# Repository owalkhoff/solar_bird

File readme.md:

# solar bird

## What is a solar bird?

There are many species of solar birds. This one (like most) feeds on sunlight through a solar cell. Its brain is made up of an ATtiny13 microcontroller. With the help of a computer (and a human) it can learn new songs. A piezo speaker is the bird's voice. A resistor limits the inrush current through the piezo when the bird starts singing. And a capacitor supplies food during shady periods.

## Code

The solar bird can be programmed via the ISP header using a [USBasp programmer](https://www.fischl.de/usbasp/) and the command `make flash`.

The code can be found in [Urban Bieri's repository](https://github.com/schaum/solarBird). He developed it together with [Christoph Haberer (ChrisMicro)](https://github.com/ChrisMicro) based on Christoph's original code from 2008.

## Images

Here is a rendering of the PCB front, with components:

A beautiful solar bird made by a student at Kollegi Schwyz in September 2020 (workshop with Felix Bänteli, using an older PCB version):

## PDFs

The schematic:

[solar_bird_schematic.pdf](pdf/solar_bird_schematic.pdf)

Use a 3V or 4V solar cell.

## KiCad files

The schematic and layout were drawn in KiCad 5.1.8. You can find the project [in this directory](kicad).

I am experimenting with different PCB layouts that share the same schematic. Therefore there are three project files between which one can switch in the project tree (using the right mouse button):

* solar_bird.pro (to edit the schematic)
* solar_bird_pcb_01.pro (to edit layout version 1)
* solar_bird_pcb_02.pro (to edit layout version 2)

## License

CC .. ..

## To dos

* Arduino code as an alternative to main.c & makefile?
* Provide a guide for tweaking the code
* Program via [audio bootloader](https://github.com/ATtinyTeenageRiot/TinyAudioBoot) and corresponding hardware? (We likely need to switch to ATtiny45 or 85)
* Add alternative footprints for SMD components?
* Add labels in copper layer for DIY etched version
* Plot PDF and Gerber files for production
* Correct GitHub link in label on silkscreen layer
* Add license

## Research

* Where and when did this solar bird first appear - SGMK diy-makeaway? Who was there?

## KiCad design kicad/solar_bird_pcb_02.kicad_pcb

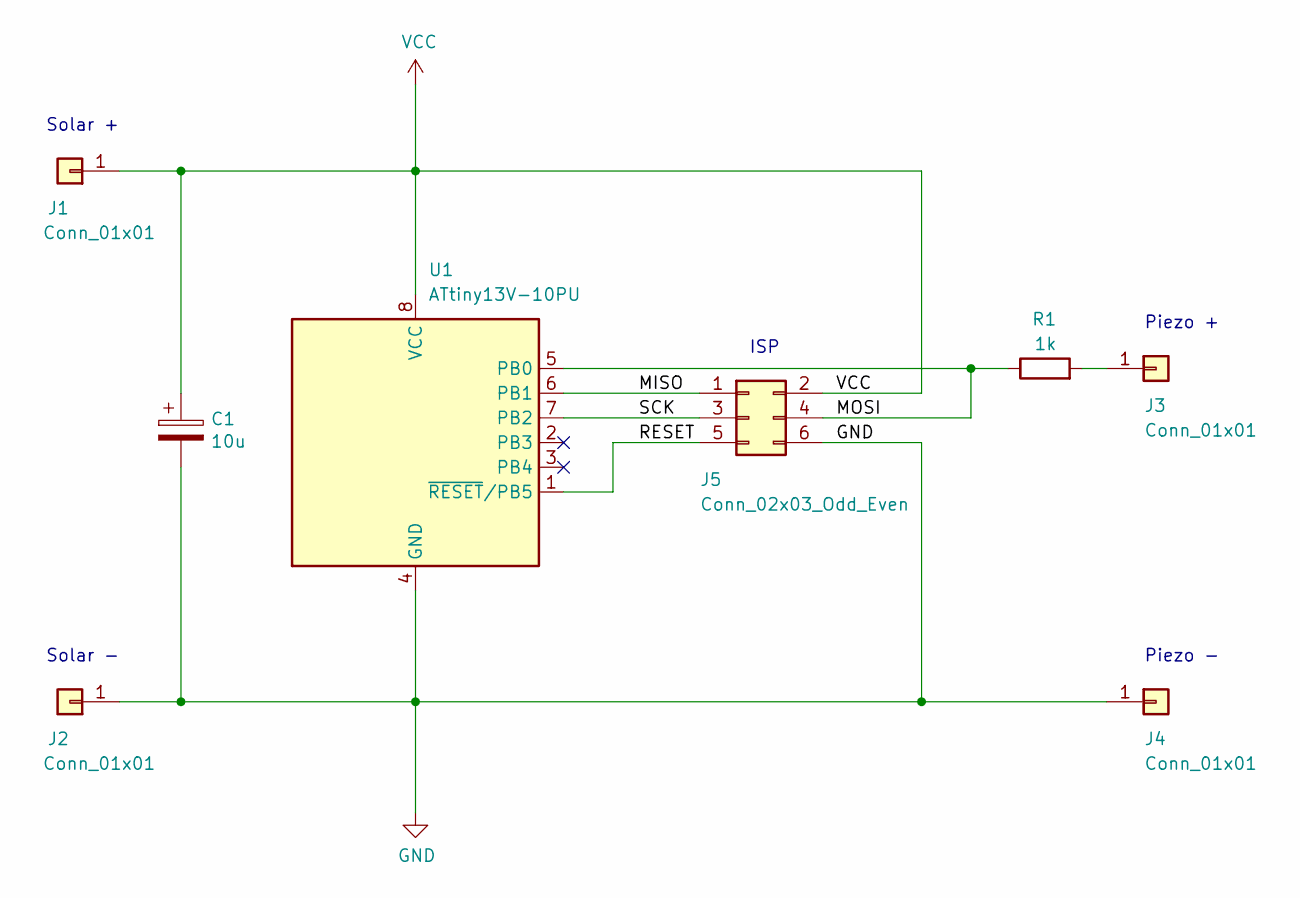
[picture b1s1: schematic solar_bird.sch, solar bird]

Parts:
C1: 10u; CP_Radial_D5.0mm_P2.50mm
J1, J2, J3, J4: Conn_01x01; Pin_D1.0mm_L10.0mm
J5: Conn_02x03_Odd_Even; PinHeader_2x03_P2.54mm_Vertical
R1: 1k; R_Axial_DIN0207_L6.3mm_D2.5mm_P10.16mm_Horizontal
U1: ATtiny13V-10PU; DIP-8_W7.62mm

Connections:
/MISO: J5.1, U1.6 (PB1)
/MOSI: J5.4, R1.1, U1.5 (PB0)
/RESET: J5.5, U1.1 (~RESET~/PB5)
/SCK: J5.3, U1.7 (PB2)
GND: C1.2, J2.1, J4.1, J5.6, U1.4 (GND)
unnamed: J3.1, R1.2
VCC: C1.1, J1.1, J5.2, U1.8 (VCC)

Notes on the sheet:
Piezo +
Piezo -
Solar +
Solar -
ISP

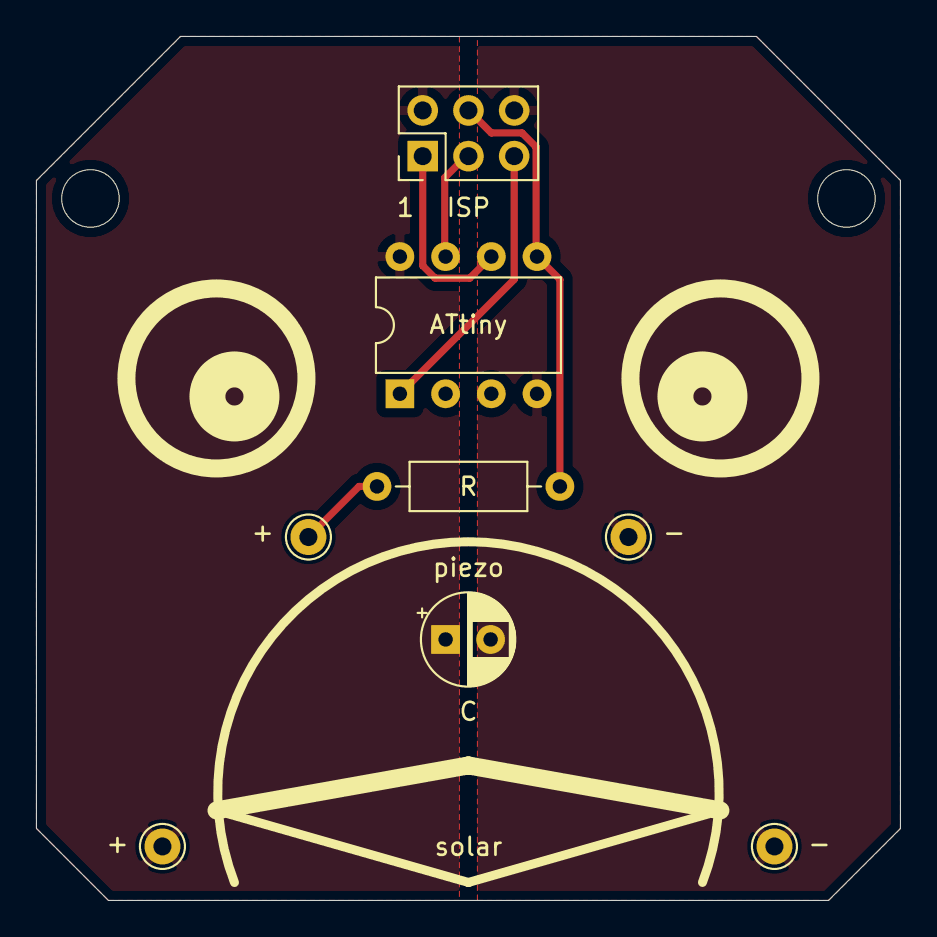
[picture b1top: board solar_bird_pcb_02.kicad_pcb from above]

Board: 2 copper layers, 48.0 x 48.0 mm, 8 parts (0 on the bottom side), 7 nets.

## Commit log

2020-11-10 Fix links in readme
2020-11-10 Fix typo
2020-11-18 Bird pcb layout
2020-11-18 Add image
